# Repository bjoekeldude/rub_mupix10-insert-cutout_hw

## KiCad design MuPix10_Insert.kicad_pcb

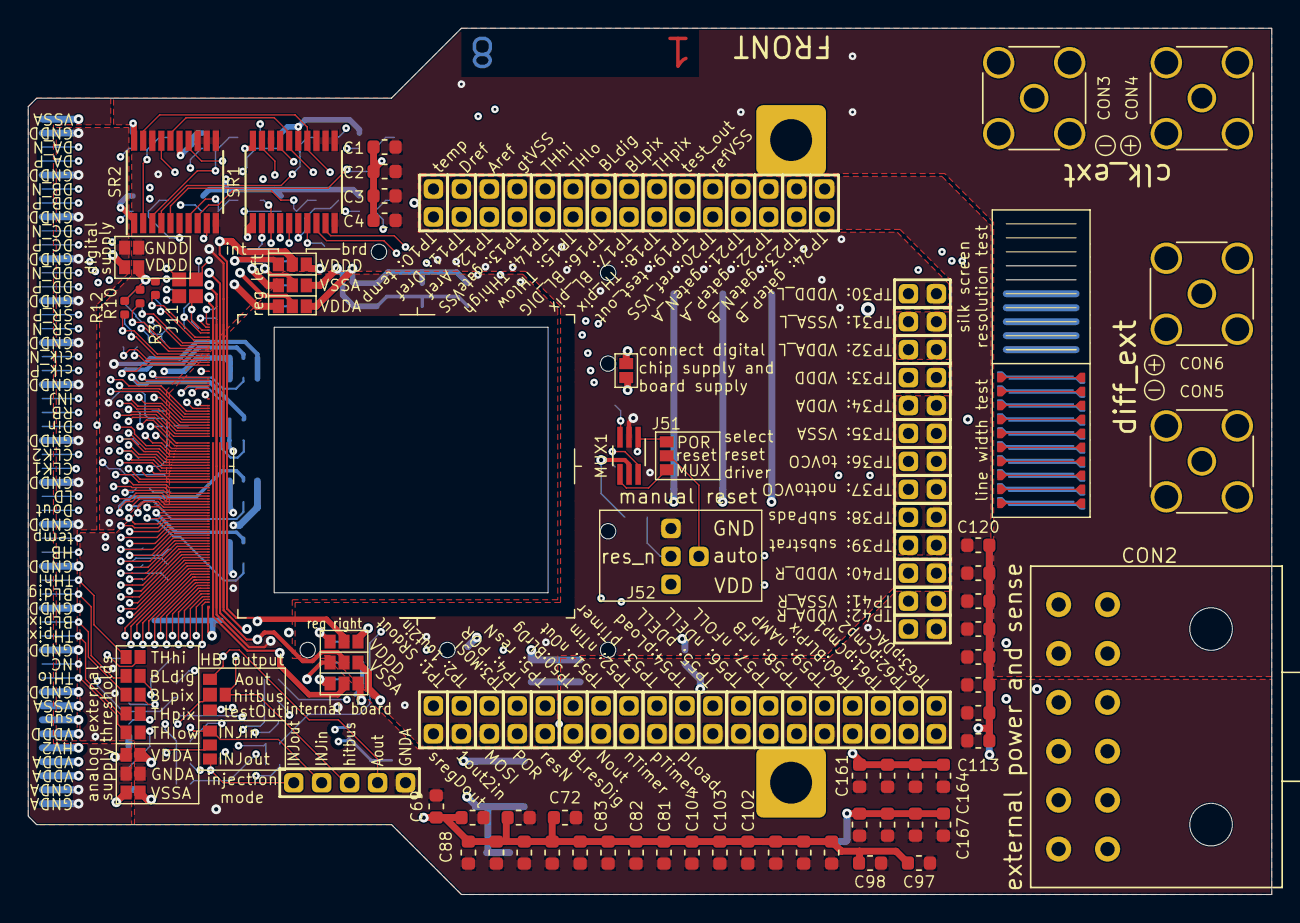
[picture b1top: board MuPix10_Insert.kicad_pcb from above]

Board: 8 copper layers, 89.0 x 62.0 mm, 277 parts (0 on the bottom side), 145 nets.

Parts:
C1, C2, C3, C4, C5, C6, C7, C8, C65, C66, C67, C68, C69, C70, C71, C72, C129, C130, C131, C132, C133, C134, C135, C136: 10n; C_0603_1608Metric
C17, C18, C19, C20, C21, C22, C23, C24, C81, C82, C83, C84, C85, C86, C87, C88, C145, C146, C147, C148, C149, C150, C151, C152, C204, C206, C210, C212, C214: 100n; C_0603_1608Metric
C33, C34, C35, C36, C37, C38, C39, C40, C97, C98, C99, C100, C101, C102, C103, C104, C161, C162, C163, C164, C165, C166, C167, C168: 1µ; C_0603_1608Metric
C49, C50, C51, C52, C53, C54, C55, C56, C113, C114, C115, C116, C117, C118, C119, C120, C177, C178, C179, C180, C181, C182, C183, C184: 10µ; C_0603_1608Metric
C193, C194, C201: 100n 100V; C_0603_1608Metric
C197, C198, C202: 10n 100V; C_0603_1608Metric
C203, C205, C209, C211, C213: 10n; C_0402_1005Metric
C207, C208: 100pF; C_0402_1005Metric
CON1: Samtec_MB1-150-01
CON2: Conn_02x06_Top_Bottom; Molex_172316_12pin
CON3, CON4, CON5, CON6: Conn_Coaxial_Power; SMA_Amphenol_132134_Vertical
H1, H2, H3, H4, H5, H6, H8: MountingHole; drill_1,1mm
J1, J3, J4, J5, J6, J7, J8, J9, J12, J13, J14, J17, J18, J21, J22, J29, J30, J35, J37, J38, J39, J40, J53, J54, J55, J56, J57, J58: SolderJumper; solder_jumper_2
J2, J15, J16, J19, J20, J23, J24, J25, J26, J27, J28, J31, J32, J33, J34, J41, J44, J51: jumper_3; solder_jumper_3
J10, J11: jumper_2x2; solder_jumper_2x2
J36, J42, J43, J45, J46, J47, J48, J49, J50: jumper_3+1; solder_jumper_3+1
J52: jumper_3+1; pin_jumper_3+1
MPX1: MuPix10_Bondpads; MuPix10_Insert_noPads
MUX1: TC7SB3157CFU; SOT-363_SC-70-6_Handsoldering
PAD1, PAD2: MountingHole_Pad; mounting_hole_3mm
R1, R2, R3, R4, R5, R6, R7, R8, R9, R10, R11, R12: 100; R_0402_1005Metric
R13, R14: inf; R_0402_1005Metric
R15, R16, R21, R22, R23, R24, R25, R26, R27, R28, R29, R30, R31, R32, R33, R34: 10k; R_0603_1608Metric
R17, R18: inf; R_0603_1608Metric
R19, R20: 1k; R_0402_1005Metric
SR1, SR2: 74LVC8T595-TSSOP20; TSSOP-20_4.4x6.5mm_P0.65mm
TP1, TP2, TP3, TP4, TP5, TP10, TP11, TP12, TP13, TP14, TP15, TP16, TP17, TP18, TP19, TP20, TP21, TP22, TP23, TP24, TP30, TP31, TP32, TP33, TP34, TP35, TP36, TP37, TP38, TP39, TP40, TP41, TP42, TP50, TP51, TP52, TP53, TP54, TP55, TP56, TP57, TP58, TP59, TP60, TP61, TP62, TP63: TestPoint_2Pole; pin_jumper_2
TP70, TP71, TP72, TP73, TP74: TestPoint; pin_jumper_1

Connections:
/External Connectors/GNDA_sense: CON2.7, CON2.9
/Filter/Filters for Analog Signals/not_to_VCO_buffer: C208.1, R14.2
/Filter/Filters for Analog Signals/to_VCO_buffer: C207.1, R13.2
/Multiplexer for Setting ResN/resn_MUX: J51.2, MUX1.4
/Multiplexer for Setting ResN/resn_automatic: J51.0, J52.2
A_0: J49.0, MPX1.25
A_0_shiftreg: J49.2, R21.1, SR2.2
A_1: J47.0, MPX1.27
A_1_shiftreg: J47.2, R22.1, SR2.3
A_2: J45.0, MPX1.29
A_2_shiftreg: J45.2, R23.1, SR2.4
A_3: J42.0, MPX1.31
A_3_shiftreg: J42.2, R24.1, SR2.5
A_out: J36.1, MPX1.67, R20.2, TP73.1
A_ref: MPX1.63, TP12.1
BL_DIG: C205.1, C206.1, J39.2, MPX1.70, TP16.1
BL_DIG_edgecon: CON1.16, J39.1
BL_RES_DIG: MPX1.79, TP50.1
BL_R_pix: MPX1.89, TP60.1
BL_pix: C211.1, C212.1, J40.2, MPX1.71, TP17.1
BL_pix_edgecon: CON1.14, J40.1
CTRL_D_in: CON1.28, J5.2, J6.2, J7.2
CTRL_D_out: CON1.22, J2.0
CTRL_LD: CON1.23, J8.2, J9.2
CTRL_RB: CON1.29, SR2.17
CTRL_clk_1: CON1.25, J1.2, J3.2, J4.2
CTRL_clk_2: CON1.26, MPX1.28
D_ref: MPX1.59, TP11.1
GNDA: C65.2, C66.2, C67.2, C68.2, C69.2, C70.2, C71.2, C72.2, C81.2, C82.2, C83.2, C84.2, C85.2, C86.2, C87.2, C88.2, C97.2, C98.2, C99.2, C100.2, C101.2, C102.2, C103.2, C104.2, C113.2, C114.2, C115.2, C116.2, C117.2, C118.2, C119.2, C120.2, C129.2, C130.2, C131.2, C132.2, C133.2, C134.2, C135.2, C136.2, C145.2, C146.2, C147.2, C148.2, C149.2, C150.2, C151.2, C152.2, C161.2, C162.2, C163.2, C164.2, C165.2, C166.2, C167.2, C168.2, C177.2, C178.2, C179.2, C180.2, C181.2, C182.2, C183.2, C184.2, C193.2, C194.2, C197.2, C198.2, C201.2, C202.2, C203.2, C204.2, C205.2, C206.2, C207.2, C208.2, C209.2, C210.2, C211.2, C212.2, C213.2, C214.2, CON2.1, CON2.3, J12.2, J17.2, J18.2, J21.2, J22.2, J23.1, J24.1, J25.1, J26.1, J55.2, MPX1.99, R19.1, R20.1, TP10.2, TP11.2, TP12.2, TP13.2, TP14.2, TP15.2, TP16.2, TP17.2, TP18.2, TP19.2, TP20.2, TP21.2, TP22.2, TP23.2, TP24.2, TP31.2, TP32.2, TP34.2, TP35.2, TP36.2, TP37.2, TP38.2, TP39.2, TP41.2, TP42.2, TP50.2, TP51.2, TP52.2, TP53.2, TP54.2, TP55.2, TP56.2, TP57.2, TP58.2, TP59.2, TP60.2, TP61.2, TP62.2, TP63.2, TP74.1
GNDA_edgecon: CON1.1, CON1.2, J55.1
GNDD: C1.2, C2.2, C3.2, C4.2, C5.2, C6.2, C7.2, C8.2, C17.2, C18.2, C19.2, C20.2, C21.2, C22.2, C23.2, C24.2, C33.2, C34.2, C35.2, C36.2, C37.2, C38.2, C39.2, C40.2, C49.2, C50.2, C51.2, C52.2, C53.2, C54.2, C55.2, C56.2, CON2.5, CON3.2, CON4.2, CON5.2, CON6.2, J12.1, J29.2, J30.2, J31.1, J32.1, J33.1, J34.1, J42.1, J43.1, J44.1, J45.1, J46.1, J47.1, J48.1, J49.1, J50.1, J52.1, J53.2, MPX1.96, MUX1.2, R15.2, R16.2, R18.2, R21.2, R22.2, R23.2, R24.2, R25.2, R26.2, R27.2, R28.2, R29.2, R30.2, R31.2, R32.2, R33.2, R34.2, SR1.10, SR1.11, SR1.12, SR1.13, SR1.18, SR2.10, SR2.11, SR2.12, SR2.13, SR2.18, TP1.2, TP2.2, TP3.2, TP4.2, TP5.2, TP30.2, TP33.2, TP40.2
GNDD_edgecon: CON1.9, CON1.12, CON1.15, CON1.18, CON1.21, CON1.24, CON1.27, CON1.31, CON1.34, CON1.37, CON1.40, CON1.43, CON1.46, CON1.49, J53.1
HB_edgecon: CON1.19, J36.0
HV_2: C201.1, C202.1, CON1.5, J14.1
LD_TDAC: MPX1.34, R31.1, SR1.4
LD_VDAC: MPX1.42, R34.1, SR1.7
LD_bias: MPX1.40, R33.1, SR1.6
LD_column: MPX1.32, R30.1, SR1.3
LD_config: MPX1.38, R32.1, SR1.5
LD_test: MPX1.30, R29.1, SR1.2
POR: J51.1, MPX1.53, MUX1.1, TP4.1
SPI_CSB: J9.1, MPX1.49
SPI_MISO: J2.1, MPX1.51
SPI_MOSI: J7.1, MPX1.45, TP3.1
SPI_SCK: J4.1, MPX1.47
S_in_N: J11.4, MPX1.3, R4.2
S_in_P: J10.3, MPX1.4, R4.1
TH_high: C203.1, C204.1, J35.2, MPX1.68, TP14.1
TH_high_edgecon: CON1.17, J35.1
TH_low: C209.1, C210.1, J37.2, MPX1.69, TP15.1
TH_low_edgecon: CON1.10, J37.1
TH_pix: C213.1, C214.1, J38.2, MPX1.72, TP18.1
TH_pix_edgecon: CON1.13, J38.1
VDDA: C65.1, C66.1, C67.1, C68.1, C69.1, C70.1, C71.1, C72.1, C81.1, C82.1, C83.1, C84.1, C85.1, C86.1, C87.1, C88.1, C97.1, C98.1, C99.1, C100.1, C101.1, C102.1, C103.1, C104.1, C113.1, C114.1, C115.1, C116.1, C117.1, C118.1, C119.1, C120.1, CON2.2, J13.2, J19.2, J20.2, J23.2, J24.2, J25.2, J26.2, J56.2, TP34.1
VDDA_edgecon: CON1.3, CON1.4, J56.1
VDDA_left: J19.0, MPX1.100, TP32.1
VDDA_right: J20.0, MPX1.101, TP42.1
VDDD: C1.1, C2.1, C3.1, C4.1, C5.1, C6.1, C7.1, C8.1, C17.1, C18.1, C19.1, C20.1, C21.1, C22.1, C23.1, C24.1, C33.1, C34.1, C35.1, C36.1, C37.1, C38.1, C39.1, C40.1, C49.1, C50.1, C51.1, C52.1, C53.1, C54.1, C55.1, C56.1, CON2.6, J13.1, J27.2, J28.2, J31.2, J32.2, J33.2, J34.2, J58.2, TP33.1
VDDD_board: J42.3, J43.3, J44.2, J45.3, J46.3, J47.3, J48.3, J49.3, J50.3, J52.3, J54.2, J58.1, MUX1.5, R1.1, R3.1, R5.1, R7.1, R9.1, R10.1, R11.1, R12.1, R17.1, SR1.1, SR1.15, SR1.20, SR2.1, SR2.15, SR2.20
VDDD_edgecon: CON1.6, J54.1
VDDD_left: J27.0, MPX1.94, TP30.1
VDDD_right: J28.0, MPX1.95, TP40.1
VSSA: C129.1, C130.1, C131.1, C132.1, C133.1, C134.1, C135.1, C136.1, C145.1, C146.1, C147.1, C148.1, C149.1, C150.1, C151.1, C152.1, C161.1, C162.1, C163.1, C164.1, C165.1, C166.1, C167.1, C168.1, C177.1, C178.1, C179.1, C180.1, C181.1, C182.1, C183.1, C184.1, CON2.4, J15.2, J16.2, J57.2, TP35.1
VSSA_edgecon: CON1.8, CON1.50, J57.1
VSSA_left: J15.0, MPX1.97, TP31.1
VSSA_right: J16.0, MPX1.98, TP41.1
V_in_AL: J25.0, MPX1.19
V_in_AR: J26.0, MPX1.60
V_in_DL: J33.0, MPX1.15
V_in_DR: J34.0, MPX1.56
V_out_AL: J19.1, J21.1, MPX1.21
V_out_AR: J20.1, J22.1, MPX1.62
V_out_DL: J27.1, J29.1, MPX1.18
V_out_DR: J28.1, J30.1, MPX1.58
V_out_SL: J15.1, J17.1, MPX1.22
V_out_SR: J16.1, J18.1, MPX1.64
WR_ext: J43.0, MPX1.48
WR_ext_shiftreg: J43.2, R28.1, SR2.9
clk_N: CON1.33, MPX1.1, R2.2
clk_P: CON1.32, MPX1.2, R2.1
clk_ext_N: CON3.1, MPX1.41, R8.2
clk_ext_P: CON4.1, MPX1.43, R8.1
connect_resistor: J50.0, MPX1.33
connect_resistor_shiftreg: J50.2, R25.1, SR2.6
data_A_N: CON1.48, MPX1.6, R1.2
data_A_P: CON1.47, MPX1.5, R3.2
data_B_N: CON1.45, MPX1.8, R5.2
data_B_P: CON1.44, MPX1.7, R7.2
data_C_N: CON1.42, MPX1.10, R9.2
data_C_P: CON1.41, MPX1.9, R10.2
data_D_N: CON1.39, MPX1.12, R11.2
data_D_P: CON1.38, MPX1.11, R12.2
data_between_shiftregs: SR1.14, SR2.19, TP2.1
differential_ext_N: CON5.1, J11.3
differential_ext_P: CON6.1, J10.4
enable_SC: J46.0, MPX1.39
enable_SC_shiftreg: J46.2, R27.1, SR2.8
gate_VSS: MPX1.65, TP13.1
gate_n_A: MPX1.75, TP21.1
gate_n_B: MPX1.77, TP23.1
gate_p_A: MPX1.76, TP22.1
gate_p_B: MPX1.78, TP24.1
hitbus: J36.2, MPX1.54, R19.2, TP71.1
inject_in: J41.1, MPX1.44, TP70.1
inject_out: J41.2, MPX1.66, TP72.1
injection: CON1.30, J41.0
n_AMP: MPX1.88, TP59.1
n_DELL: MPX1.85, TP56.1
n_FB: MPX1.87, TP58.1
n_FOLL: MPX1.86, TP57.1
n_out: MPX1.80, TP51.1
n_timer: MPX1.81, TP52.1
not_to_VCO: MPX1.36, R14.1, TP37.1
p_COMP_1: MPX1.90, TP61.1
p_COMP_2: MPX1.91, TP62.1
p_DAC: MPX1.92, TP63.1
p_DELL: MPX1.84, TP55.1
p_load: MPX1.83, TP54.1
p_timer: MPX1.82, TP53.1
ref_VSS: MPX1.74, TP20.1
res_n: J52.0, MPX1.55, R17.2, R18.1, TP5.1
res_n_software: MUX1.3, R16.1, SR1.9
serial_D_in: J5.1, MPX1.24
serial_clk: J1.1, MPX1.26
shiftreg_D_in: J6.1, SR1.19
shiftreg_D_out: J2.2, SR2.14, TP1.1
shiftreg_LD: J8.1, SR1.17
shiftreg_clk: J3.1, SR1.16, SR2.16
shunt_AL: J23.0, MPX1.20
shunt_AR: J24.0, MPX1.61
shunt_DL: J31.0, MPX1.17
shunt_DR: J32.0, MPX1.57
substrate: C193.1, C194.1, C197.1, C198.1, CON1.7, MPX1.93, TP39.1
substrate_pads: J14.2, MPX1.16, TP38.1
sync_res_N: J11.1, MPX1.14, R6.2
sync_res_P: J10.2, MPX1.13, R6.1
sync_res_edgecon_N: CON1.35, J11.2
sync_res_edgecon_P: CON1.36, J10.1
temperature_diode: CON1.20, MPX1.23, TP10.1
test_out: J36.3, MPX1.73, TP19.1
to_VCO: MPX1.35, R13.1, TP36.1
use_POR: MUX1.6, R15.1, SR1.8
use_SPI: J48.0, MPX1.37
use_SPIRO: J44.0, MPX1.46
use_SPI_shiftreg: J48.2, R26.1, SR2.7

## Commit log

2021-11-12 initial
2021-11-12 delets unused files
